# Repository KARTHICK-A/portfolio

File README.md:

# Karthick A — Portfolio

Personal site of **Karthick A**, Embedded Product Engineer in Chennai — automotive ECU
electronics, custom PCB design, embedded C/C++ and industrial IoT.

**Live:** https://karthick-a.github.io/portfolio/

## The idea

The page is built like a board, not like a résumé. The hero renders a real 3D circuit
board (three.js/WebGL) where **every IC is one project** — hover a chip to see what it is,
click it to open that project's card below. Projects are cards with reference designators
(U1–U7), skills a layer stack-up, contact links test points. No dates, no timeline.

The board is never the only way in: a row of U1–U7 links under it does the same thing for
keyboard, screen-reader and touch users, and a **Pause motion** switch (plus the OS
reduced-motion setting) stops all self-running animation.

## Structure

```
index.html            markup and all copy
styles.css            styling — dark substrate, copper accents, silkscreen type
script.js             3D board, chip→project navigation, scroll reveal + progress
assets/
  vendor/three.min.js three.js r160 (deprecated UMD build), vendored
  images/og.png       1200×630 link-preview image
  images/profile/     profile photo
```

Static, no build step. If JavaScript or WebGL is unavailable the board panel is removed
and the page still reads completely. When the visitor prefers reduced motion the board is
still drawn and stays clickable, but nothing animates on its own — no auto-rotation,
float, LED blink or ticker.

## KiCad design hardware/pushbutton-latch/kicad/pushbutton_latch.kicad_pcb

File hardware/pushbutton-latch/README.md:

# Push-button latch + STM32L0 gesture power controller (rev A, draft)

One button switches a Li-ion powered board **on**, lets the MCU decode
**tap / double tap / triple tap / 1 s / 3 s / 5 s** gestures, and puts the board
into **Sleep**, **Deep sleep** or **fully OFF**. A ~10 s hold is a hardware
override that works even if the firmware has crashed.

> **Status: draft, not built, not tested on hardware.** The datasheets could
> not be downloaded in the environment this was designed in (see
> `datasheets/README.md`). Pinouts come from KiCad's official libraries; key
> electrical figures come from web-search summaries of the datasheets. Work
> through the **Verify before ordering** list first.

## Folder

| Path | What |
|---|---|
| `kicad/` | KiCad 10 project: schematic + PCB (footprints placed, **not routed**) |
| `exports/` | `schematic.pdf`, `pcb_placement.pdf`, `bom.csv`, `netlist.net`, ERC/DRC reports |
| `firmware/` | STM32L0 C code: gesture decoder (host-tested), power modes, example `main` |
| `datasheets/` | datasheet links, figures used, `download.sh` |
| `tools/` | Python scripts that generate the schematic/PCB from `design.py` and check the netlist |

Open `kicad/pushbutton_latch.kicad_pro` in KiCad 10. It uses only KiCad's
standard libraries.

## How it works

```
USB-C 5V ──► MCP73831 charger ──► VBAT (1S Li-ion, protected cell)
                                    │
                    ┌───────────────┼──────────────────────────┐
                    ▼               ▼                          │
   button ──► STM6601 latch    TPS7A05 3.3 V LDO ──► +3V3 ──► STM32L031K6
   (SW1)      (always on,        IN = VBAT                     │
               0.6 µA standby)   EN = latch EN ◄───────────────┘
                 │  EN ──────────────┘         PS_HOLD (PA1): MCU pulls low = OFF
                 │  ~PB_OUT ─────────────────► PA0 (EXTI0 + WKUP1): gesture timing
                 │  ~INT ────────────────────► PA2
                 │  ~VCC_LO ─────────────────► PA3 (battery low)
                 └  ~RST ────────────────────► NRST
```

* **On:** pressing SW1 makes the STM6601 raise EN, which enables the LDO, which
  powers the MCU. R8 pulls PS_HOLD high as soon as 3.3 V is up, confirming
  power-on.
* **Gestures:** the STM6601's open-drain `~PB_OUT` copies the button state to
  PA0, so the MCU can time presses without battery voltage reaching its pins.
* **Off:** the MCU drives PS_HOLD low. The latch drops EN, the LDO shuts down
  and the MCU loses power. The battery then only supplies the STM6601 standby
  current. Charging via USB still works while the board is off.
* **Hardware override:** R6 ties `~SR` to `~PB`. Holding the button for about
  10 s (C4 = 1 µF at ~10 s/µF) triggers the STM6601 Smart Reset.
* **Battery voltage:** R15/R16 divide the latch EN output, which sits at VBAT
  while on and 0 V while off, so the divider draws nothing when the board is off.

## Gestures and power modes (firmware defaults, editable)

| Gesture | Action |
|---|---|
| press (while off) | power on |
| 1 tap | action A (example: toggle LED) |
| 2 taps | action B |
| 3 taps | **Deep sleep**: STM32 Standby, RAM lost, button wakes it and it restarts |
| hold 1 s | **Sleep**: STM32 Stop, RAM kept, any press resumes |
| hold 3 s | action C |
| hold 5 s | **OFF**: PS_HOLD low |
| hold ~10 s | STM6601 Smart Reset, hardware override |
| 30 s idle | automatic Sleep |
| battery low (`~VCC_LO`) | blink, then OFF |

Estimated battery current. These are typical values added up, not measurements:

| Mode | Adds up to | Main contributor |
|---|---|---|
| OFF | ≈ 0.6 µA + LDO shutdown current + charger reverse leakage (both still to be checked) | STM6601 standby |
| Deep sleep (Standby) | ≈ 6 + 1 + 0.23 + 0.45 ≈ **7.7 µA** | STM6601 operating current (6 µA) |
| Sleep (Stop + RTC) | ≈ 6 + 1 + 0.6 + 0.45 ≈ **8 µA** | STM6601 operating current |

Honest note: Sleep and Deep sleep are within ~0.4 µA of each other because
the latch's own 6 µA operating current dominates both. Real savings come from
OFF. Replacing the STM6601 with a **MAX16150** (< 20 nA, see
`datasheets/README.md`) is the main rev B improvement, once its pinout is
confirmed.

## Verification done

* KiCad 10.0.6 **ERC: 0 errors, 0 warnings** (`exports/erc_report.txt`).
* Netlist exported by KiCad compared automatically against the connection
  table in `tools/design.py`: all 26 nets match (`tools/verify_net.py`).
* PCB **DRC: 0 violations** (no courtyard overlaps or clearance problems). The
  91 "unconnected items" are expected because the board isn't routed yet.
* Gesture decoder: 13 host unit tests pass
  (`cd firmware/test && gcc -I.. ../button_gesture.c test_gesture.c -o t && ./t`).
* **Not done:** `board_power.c` has not been compiled against STM32CubeL0,
  nothing has been run on hardware, and the PCB has not been routed.

## Verify before ordering

1. **STM6601 ordering code:** EN must be **active-high push-pull**. Choose the
   VCC_LO threshold and tON_BLANK for a 1S Li-ion cell (the ordering-option
   table is in the datasheet).
2. **STM6601 `~SR` tied to `~PB` (R6):** confirm this gives single-button
   Smart Reset, and whether it asserts RST or drops EN on this variant. If
   unwanted, remove R6 and pull `~SR` up to VBAT.
3. **STM6601 Vref (pin 3):** left unconnected; confirm no capacitor is needed.
   Also confirm whether `~PB` has an internal pull-up (R5 = 1 MΩ is fitted
   either way; it only draws current while pressed).
4. **STM32L0 WKUP1:** check the edge polarity and what happens if PA0 is
   already high on Standby entry (RM0377). The firmware waits for the button
   to be released first. If Standby wake is unreliable, use Stop for both
   sleep modes (≈0.1 µA difference).
5. **TPS7A05:** input/output capacitor values and shutdown current.
6. **MCP73831:** R3 = 4.7 kΩ gives ≈213 mA. Keep it at or below 1C of your
   cell. Check reverse leakage from VBAT when USB is unplugged.
7. **Battery:** use a cell with its own protection PCB. This board has no
   over-discharge or short-circuit protection of its own.
8. **USB-C J1:** check which side the plug opens to before finishing placement.

## Next steps

1. Download the datasheets (`datasheets/download.sh`) and go through the list above.
2. Route the PCB in KiCad 10 (2 layers; pour GND on the bottom layer). Current
   placement is a starting point.
3. Generate the STM32CubeMX project for STM32L031K6 and add `firmware/*.c`.

## Regenerating from the scripts

The schematic and PCB are generated from `tools/design.py`. This is only
needed if you want to change the design through the scripts rather than in
KiCad. Requires KiCad 10 on Linux (uses `kicad-cli`, the `pcbnew` Python
module, and libraries under `/usr/share/kicad`). The scripts write to the
current folder:

```sh
cd hardware/pushbutton-latch/tools
python3 gen_sch.py && kicad-cli sch upgrade pushbutton_latch.kicad_sch
kicad-cli sch export netlist --format kicadsexpr -o net.net pushbutton_latch.kicad_sch && python3 verify_net.py
python3 gen_pcb.py
mv pushbutton_latch.kicad_sch pushbutton_latch.kicad_pcb ../kicad/
```

After you edit the design in KiCad itself, treat the KiCad files as the
source of truth and stop using the scripts.

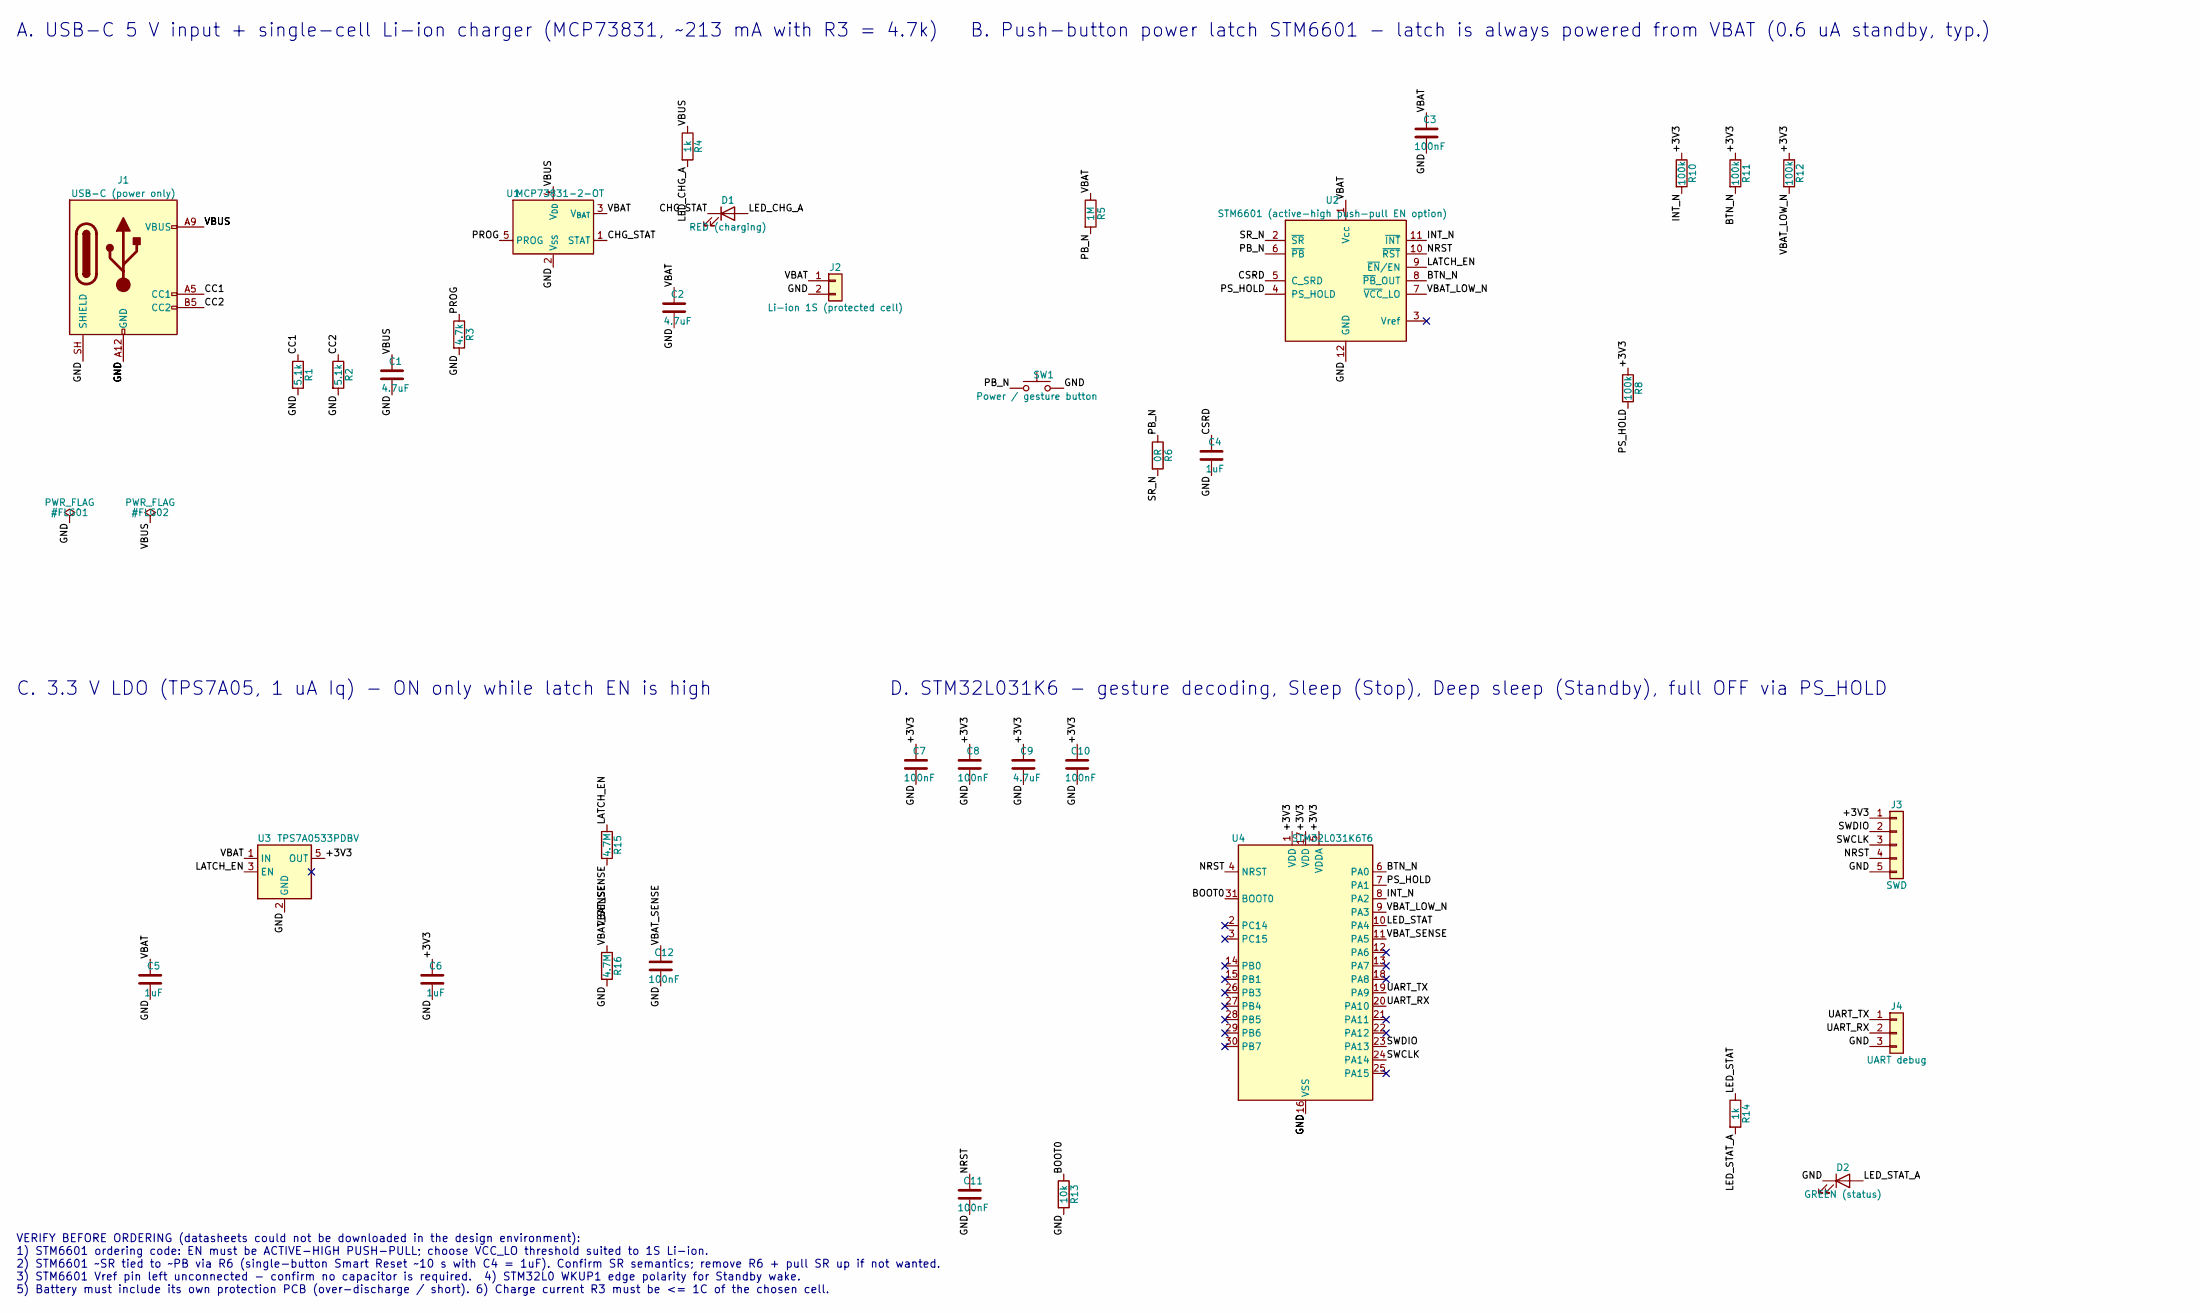
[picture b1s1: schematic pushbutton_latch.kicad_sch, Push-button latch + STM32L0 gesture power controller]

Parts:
C1, C2, C9: 4.7uF; C_0805_2012Metric
C3, C7, C8, C10, C11, C12: 100nF; C_0603_1608Metric
C4, C5, C6: 1uF; C_0603_1608Metric
D1: RED (charging); LED_0603_1608Metric
D2: GREEN (status); LED_0603_1608Metric
J1: USB-C (power only); USB_C_Receptacle_GCT_USB4125-xx-x_6P_TopMnt_Horizontal
J2: Li-ion 1S (protected cell); JST_PH_S2B-PH-K_1x02_P2.00mm_Horizontal
J3: SWD; PinHeader_1x05_P2.54mm_Vertical
J4: UART debug; PinHeader_1x03_P2.54mm_Vertical
R1, R2: 5.1k; R_0603_1608Metric
R3: 4.7k; R_0603_1608Metric
R4, R14: 1k; R_0603_1608Metric
R5: 1M; R_0603_1608Metric
R6: 0R; R_0603_1608Metric
R8, R10, R11, R12: 100k; R_0603_1608Metric
R13: 10k; R_0603_1608Metric
R15, R16: 4.7M; R_0603_1608Metric
SW1: Power / gesture button; SW_SPST_TL3342
U1: MCP73831-2-OT; SOT-23-5
U2: STM6601 (active-high push-pull EN option); TDFN-12_2x3mm_P0.5mm
U3: TPS7A0533PDBV; SOT-23-5
U4: STM32L031K6T6; LQFP-32_7x7mm_P0.8mm

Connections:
+3V3: C6.1, C7.1, C8.1, C9.1, C10.1, J3.1, R8.1, R10.1, R11.1, R12.1, U3.5 (OUT), U4.1 (VDD), U4.5 (VDDA), U4.17 (VDD)
BOOT0: R13.1, U4.31 (BOOT0)
BTN_N: R11.2, U2.8 (~PB_OUT), U4.6 (PA0)
CC1: J1.A5 (CC1), R1.1
CC2: J1.B5 (CC2), R2.1
CHG_STAT: D1.1 (K), U1.1 (STAT)
CSRD: C4.1, U2.5 (C_SRD)
GND: C1.2, C2.2, C3.2, C4.2, C5.2, C6.2, C7.2, C8.2, C9.2, C10.2, C11.2, C12.2, D2.1 (K), J1.A12 (GND), J1.B12 (GND), J1.SH (SHIELD), J2.2, J3.5, J4.3, R1.2, R2.2, R3.2, R13.2, R16.2, SW1.2, U1.2 (V_{SS}), U2.12 (GND), U3.2 (GND), U4.16 (VSS), U4.32 (VSS)
INT_N: R10.2, U2.11 (~INT), U4.8 (PA2)
LATCH_EN: R15.1, U2.9 (~EN/EN), U3.3 (EN)
LED_CHG_A: D1.2 (A), R4.2
LED_STAT: R14.1, U4.10 (PA4)
LED_STAT_A: D2.2 (A), R14.2
NRST: C11.1, J3.4, U2.10 (~RST), U4.4 (NRST)
PB_N: R5.2, R6.1, SW1.1, U2.6 (~PB)
PROG: R3.1, U1.5 (PROG)
PS_HOLD: R8.2, U2.4 (PS_HOLD), U4.7 (PA1)
SR_N: R6.2, U2.2 (~SR)
SWCLK: J3.3, U4.24 (PA14)
SWDIO: J3.2, U4.23 (PA13)
UART_RX: J4.2, U4.20 (PA10)
UART_TX: J4.1, U4.19 (PA9)
VBAT: C2.1, C3.1, C5.1, J2.1, R5.1, U1.3 (V_{BAT}), U2.1 (Vcc), U3.1 (IN)
VBAT_LOW_N: R12.2, U2.7 (~VCC_LO), U4.9 (PA3)
VBAT_SENSE: C12.1, R15.2, R16.1, U4.11 (PA5)
VBUS: C1.1, J1.A9 (VBUS), J1.B9 (VBUS), R4.1, U1.4 (V_{DD})

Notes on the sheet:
A. USB-C 5 V input + single-cell Li-ion charger (MCP73831, ~213 mA with R3 = 4.7k)
C. 3.3 V LDO (TPS7A05, 1 uA Iq) - ON only while latch EN is high
D. STM32L031K6 - gesture decoding, Sleep (Stop), Deep sleep (Standby), full OFF via PS_HOLD
B. Push-button power latch STM6601 - latch is always powered from VBAT (0.6 uA standby, typ.)
VERIFY BEFORE ORDERING (datasheets could not be downloaded in the design environment): 1) STM6601 ordering code: EN must be ACTIVE-HIGH PUSH-PULL; choose VCC_LO threshold suited to 1S Li-ion. 2) STM6601 ~SR tied to ~PB via R6 (single-button Smart Reset ~10 s with C4 = 1uF). Confirm SR semantics; re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

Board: 2 copper layers, 37 parts (0 on the bottom side), 26 nets, no tracks yet.

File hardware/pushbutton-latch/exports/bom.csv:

"Refs","Value","Footprint","Qty","Note"
"C1,C2,C9","4.7uF","Capacitor_SMD:C_0805_2012Metric","3",""
"C3,C7,C8,C11,C12","100nF","Capacitor_SMD:C_0603_1608Metric","5",""
"C4","1uF","Capacitor_SMD:C_0603_1608Metric","1","tSRD ~ 10 s/uF typ -> ~10 s hardware override"
"C5,C6","1uF","Capacitor_SMD:C_0603_1608Metric","2",""
"C10","100nF","Capacitor_SMD:C_0603_1608Metric","1","VDDA decoupling"
"D1","RED (charging)","LED_SMD:LED_0603_1608Metric","1",""
"D2","GREEN (status)","LED_SMD:LED_0603_1608Metric","1",""
"J1","USB-C (power only)","Connector_USB:USB_C_Receptacle_GCT_USB4125-xx-x_6P_TopMnt_Horizontal","1",""
"J2","Li-ion 1S (protected cell)","Connector_JST:JST_PH_S2B-PH-K_1x02_P2.00mm_Horizontal","1",""
"J3","SWD","Connector_PinHeader_2.54mm:PinHeader_1x05_P2.54mm_Vertical","1",""
"J4","UART debug","Connector_PinHeader_2.54mm:PinHeader_1x03_P2.54mm_Vertical","1",""
"R1","5.1k","Resistor_SMD:R_0603_1608Metric","1","USB-C sink Rd on CC1"
"R2","5.1k","Resistor_SMD:R_0603_1608Metric","1","USB-C sink Rd on CC2"
"R3","4.7k","Resistor_SMD:R_0603_1608Metric","1","Charge current = 1000V/R_PROG(kOhm) ~ 213 mA"
"R4,R14","1k","Resistor_SMD:R_0603_1608Metric","2",""
"R5","1M","Resistor_SMD:R_0603_1608Metric","1","PB pull-up; harmless if STM6601 has internal pull-up"
"R6","0R","Resistor_SMD:R_0603_1608Metric","1","Single-button Smart Reset (hold ~10 s). Remove to disable"
"R8","100k","Resistor_SMD:R_0603_1608Metric","1","Holds PS_HOLD high in MCU Standby; MCU drives low = OFF"
"R10-R12","100k","Resistor_SMD:R_0603_1608Metric","3",""
"R13","10k","Resistor_SMD:R_0603_1608Metric","1",""
"R15","4.7M","Resistor_SMD:R_0603_1608Metric","1","Divider fed from EN (=VBAT when ON, 0 V when OFF)"
"R16","4.7M","Resistor_SMD:R_0603_1608Metric","1",""
"SW1","Power / gesture button","Button_Switch_SMD:SW_SPST_TL3342","1",""
"U1","MCP73831-2-OT","Package_TO_SOT_SMD:SOT-23-5","1",""
"U2","STM6601 (active-high push-pull EN option)","Package_DFN_QFN:TDFN-12_2x3mm_P0.5mm","1","Order code must give active-high push-pull EN; pick VCC_LO threshold for 1S Li-ion"
"U3","TPS7A0533PDBV","Package_TO_SOT_SMD:SOT-23-5","1",""
"U4","STM32L031K6T6","Package_QFP:LQFP-32_7x7mm_P0.8mm","1",""

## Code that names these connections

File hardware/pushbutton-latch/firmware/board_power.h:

/*
 * board_power.h - power modes for the STM6601 + STM32L031K6 board.
 *
 * Pin map (matches hardware/pushbutton_latch.kicad_sch):
 *   PA0  BTN_N       STM6601 ~PB_OUT (open drain, 100k pull-up) - low while pressed.
 *                    EXTI0 for Stop wake-up, SYS_WKUP1 for Standby wake-up.
 *   PA1  PS_HOLD     STM6601 PS_HOLD (100k pull-up to 3V3). Drive LOW = power OFF.
 *   PA2  INT_N       STM6601 ~INT (open drain, 100k pull-up)
 *   PA3  VBAT_LOW_N  STM6601 ~VCC_LO (open drain, 100k pull-up) - low = battery low
 *   PA4  LED_STAT    green status LED (active high)
 *   PA5  VBAT_SENSE  ADC_IN5, VBAT/2 (4.7M/4.7M from latch EN)
 *
 * Modes:
 *   RUN         normal operation
 *   SLEEP       STM32 Stop mode: RAM + registers kept, wakes on button edge
 *               (EXTI0) in microseconds and resumes where it stopped.
 *   DEEP SLEEP  STM32 Standby: RAM lost, wakes on WKUP1 (PA0) and restarts
 *               from reset. Lowest MCU current while the latch stays ON.
 *   OFF         PS_HOLD low -> STM6601 drops EN -> LDO off -> MCU unpowered.
 *               Only the STM6601 standby current remains. Press the button to
 *               power on again.
 */
#ifndef BOARD_POWER_H
#define BOARD_POWER_H

#include <stdbool.h>
#include <stdint.h>

typedef enum { BOOT_POWER_ON, BOOT_FROM_STANDBY } boot_reason_t;

boot_reason_t board_power_init(void);      /* call first thing after HAL_Init() */
bool          board_button_pressed(void);
bool          board_battery_low(void);
uint32_t      board_vbat_mv(void);         /* approximate, see note in .c */
void          board_led(bool on);

void board_sleep(void);        /* Stop mode, returns after wake-up  */
void board_deep_sleep(void);   /* Standby, never returns (reset)    */
void board_power_off(void);    /* never returns                     */

#endif

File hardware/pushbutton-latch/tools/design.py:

"""Single source of truth for the push-button latch board.

Each part: ref, (lib, symbol), value, footprint, (x, y) on sheet [mm], {pin_number: net},
optional extra fields. Pins not listed get a no-connect flag.
"""

R0603 = "Resistor_SMD:R_0603_1608Metric"
C0603 = "Capacitor_SMD:C_0603_1608Metric"
C0805 = "Capacitor_SMD:C_0805_2012Metric"
LED0603 = "LED_SMD:LED_0603_1608Metric"


def R(ref, val, xy, a, b, **kw):
    return dict(ref=ref, lib=("Device", "R"), value=val, fp=R0603, at=xy, pins={"1": a, "2": b}, **kw)


def C(ref, val, xy, a, b, fp=C0603, **kw):
    return dict(ref=ref, lib=("Device", "C"), value=val, fp=fp, at=xy, pins={"1": a, "2": b}, **kw)


PARTS = [
    # ---------------- USB-C input + Li-ion charger (block A) ----------------
    dict(ref="J1", lib=("Connector", "USB_C_Receptacle_PowerOnly_6P"), value="USB-C (power only)",
         fp="Connector_USB:USB_C_Receptacle_GCT_USB4125-xx-x_6P_TopMnt_Horizontal", at=(40.64, 68.58),
         pins={"A9": "VBUS", "B9": "VBUS", "A12": "GND", "B12": "GND", "SH": "GND", "A5": "CC1", "B5": "CC2"}),
    R("R1", "5.1k", (73.66, 88.9), "CC1", "GND", Note="USB-C sink Rd on CC1"),
    R("R2", "5.1k", (81.28, 88.9), "CC2", "GND", Note="USB-C sink Rd on CC2"),
    C("C1", "4.7uF", (91.44, 88.9), "VBUS", "GND", fp=C0805),
    dict(ref="U1", lib=("Battery_Management", "MCP73831-2-OT"), value="MCP73831-2-OT",
         fp="Package_TO_SOT_SMD:SOT-23-5", at=(121.92, 60.96),
         pins={"4": "VBUS", "2": "GND", "3": "VBAT", "5": "PROG", "1": "CHG_STAT"}),
    R("R3", "4.7k", (104.14, 81.28), "PROG", "GND", Note="Charge current = 1000V/R_PROG(kOhm) ~ 213 mA"),
    R("R4", "1k", (147.32, 45.72), "VBUS", "LED_CHG_A"),
    dict(ref="D1", lib=("Device", "LED"), value="RED (charging)", fp=LED0603, at=(154.94, 58.42),
         pins={"2": "LED_CHG_A", "1": "CHG_STAT"}),
    C("C2", "4.7uF", (144.78, 76.2), "VBAT", "GND", fp=C0805),
    dict(ref="J2", lib=("Connector_Generic", "Conn_01x02"), value="Li-ion 1S (protected cell)",
         fp="Connector_JST:JST_PH_S2B-PH-K_1x02_P2.00mm_Horizontal", at=(175.26, 71.12),
         pins={"1": "VBAT", "2": "GND"}),

    # ---------------- Push-button latch STM6601 (block B) ----------------
    dict(ref="U2", lib=("Power_Management", "STM6601"), value="STM6601 (active-high push-pull EN option)",
         fp="Package_DFN_QFN:TDFN-12_2x3mm_P0.5mm", at=(271.78, 71.12),
         pins={"1": "VBAT", "12": "GND", "6": "PB_N", "2": "SR_N", "5": "CSRD", "4": "PS_HOLD",
               "9": "LATCH_EN", "11": "INT_N", "8": "BTN_N", "10": "NRST", "7": "VBAT_LOW_N"},
         Note="Order code must give active-high push-pull EN; pick VCC_LO threshold for 1S Li-ion"),
    C("C3", "100nF", (287.02, 43.18), "VBAT", "GND"),
    dict(ref="SW1", lib=("Switch", "SW_Push"), value="Power / gesture button",
         fp="Button_Switch_SMD:SW_SPST_TL3342", at=(213.36, 91.44),
         pins={"1": "PB_N", "2": "GND"}),
    R("R5", "1M", (223.52, 58.42), "VBAT", "PB_N", Note="PB pull-up; harmless if STM6601 has internal pull-up"),
    R("R6", "0R", (236.22, 104.14), "PB_N", "SR_N", Note="Single-button Smart Reset (hold ~10 s). Remove to disable"),
    C("C4", "1uF", (246.38, 104.14), "CSRD", "GND", Note="tSRD ~ 10 s/uF typ -> ~10 s hardware override"),
    R("R8", "100k", (325.12, 91.44), "+3V3", "PS_HOLD", Note="Holds PS_HOLD high in MCU Standby; MCU drives low = OFF"),
    R("R10", "100k", (335.28, 50.8), "+3V3", "INT_N"),
    R("R11", "100k", (345.44, 50.8), "+3V3", "BTN_N"),
    R("R12", "100k", (355.6, 50.8), "+3V3", "VBAT_LOW_N"),

    # ---------------- 3.3 V LDO + battery sense (block C) ----------------
    dict(ref="U3", lib=("Regulator_Linear", "TPS7A0533PDBV"), value="TPS7A0533PDBV",
         fp="Package_TO_SOT_SMD:SOT-23-5", at=(71.12, 182.88),
         pins={"1": "VBAT", "3": "LATCH_EN", "2": "GND", "5": "+3V3"}),
    C("C5", "1uF", (45.72, 203.2), "VBAT", "GND"),
    C("C6", "1uF", (99.06, 203.2), "+3V3", "GND"),
    R("R15", "4.7M", (132.08, 177.8), "LATCH_EN", "VBAT_SENSE", Note="Divider fed from EN (=VBAT when ON, 0 V when OFF)"),
    R("R16", "4.7M", (132.08, 200.66), "VBAT_SENSE", "GND"),
    C("C12", "100nF", (142.24, 200.66), "VBAT_SENSE", "GND"),

    # ---------------- MCU STM32L031K6 (block D) ----------------
    dict(ref="U4", lib=("MCU_ST_STM32L0", "STM32L031K6Tx"), value="STM32L031K6T6",
         fp="Package_QFP:LQFP-32_7x7mm_P0.8mm", at=(264.16, 203.2),
         pins={"1": "+3V3", "17": "+3V3", "5": "+3V3", "16": "GND", "32": "GND",
               "31": "BOOT0", "4": "NRST",
               "6": "BTN_N", "7": "PS_HOLD", "8": "INT_N", "9": "VBAT_LOW_N",
               "10": "LED_STAT", "11": "VBAT_SENSE",
               "23": "SWDIO", "24": "SWCLK", "19": "UART_TX", "20": "UART_RX"}),
    C("C7", "100nF", (190.5, 162.56), "+3V3", "GND"),
    C("C8", "100nF", (200.66, 162.56), "+3V3", "GND"),
    C("C9", "4.7uF", (210.82, 162.56), "+3V3", "GND", fp=C0805),
    C("C10", "100nF", (220.98, 162.56), "+3V3", "GND", Note="VDDA decoupling"),
    C("C11", "100nF", (200.66, 243.84), "NRST", "GND"),
    R("R13", "10k", (218.44, 243.84), "BOOT0", "GND"),
    R("R14", "1k", (345.44, 228.6), "LED_STAT", "LED_STAT_A"),
    dict(ref="D2", lib=("Device", "LED"), value="GREEN (status)", fp=LED0603, at=(365.76, 241.3),
         pins={"2": "LED_STAT_A", "1": "GND"}),
    dict(ref="J3", lib=("Connector_Generic", "Conn_01x05"), value="SWD",
         fp="Connector_PinHeader_2.54mm:PinHeader_1x05_P2.54mm_Vertical", at=(375.92, 177.8),
         pins={"1": "+3V3", "2": "SWDIO", "3": "SWCLK", "4": "NRST", "5": "GND"}),
    dict(ref="J4", lib=("Connector_Generic", "Conn_01x03"), value="UART debug",
         fp="Connector_PinHeader_2.54mm:PinHeader_1x03_P2.54mm_Vertical", at=(375.92, 213.36),
         pins={"1": "UART_TX", "2": "UART_RX", "3": "GND"}),

    # ---------------- ERC power flags ----------------
    dict(ref="#FLG01", lib=("power", "PWR_FLAG"), value="PWR_FLAG", fp="", at=(30.48, 116.84), pins={"1": "GND"}),
    dict(ref="#FLG02", lib=("power", "PWR_FLAG"), value="PWR_FLAG", fp="", at=(45.72, 116.84), pins={"1": "VBUS"}),
]

NOTES = [
    ((20.32, 25.4), "A. USB-C 5 V input + single-cell Li-ion charger (MCP73831, ~213 mA with R3 = 4.7k)"),
    ((200.66, 25.4), "B. Push-button power latch STM6601 - latch is always powered from VBAT (0.6 uA standby, typ.)"),
    ((20.32, 149.86), "C. 3.3 V LDO (TPS7A05, 1 uA Iq) - ON only while latch EN is high"),
    ((185.42, 149.86), "D. STM32L031K6 - gesture decoding, Sleep (Stop), Deep sleep (Standby), full OFF via PS_HOLD"),
    ((20.32, 262.89),
     "VERIFY BEFORE ORDERING (datasheets could not be downloaded in the design environment):\n"
     "1) STM6601 ordering code: EN must be ACTIVE-HIGH PUSH-PULL; choose VCC_LO threshold suited to 1S Li-ion.\n"
     "2) STM6601 ~SR tied to ~PB via R6 (single-button Smart Reset ~10 s with C4 = 1uF). Confirm SR semantics; remove R6 + pull SR up if not wanted.\n"
     "3) STM6601 Vref pin left unconnected - confirm no capacitor is required.  4) STM32L0 WKUP1 edge polarity for Standby wake.\n"
     "5) Battery must include its own protection PCB (over-discharge / short). 6) Charge current R3 must be <= 1C of the chosen cell."),
]
